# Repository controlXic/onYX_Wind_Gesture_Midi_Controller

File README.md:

# onYX

### Full Function Description:

OnYX is a highly versatile and ergonomic MIDI controller that combines the functionalities of wind controllers, pad controllers and gesture controllers.

It consists of 4 pieces:

* the mouthpiece: includes an air pressure sensor with which we control the Velocity, Breath Controller (CC2), Volume (CC7) and Expression (CC11)

* the left handpiece: includes 4 touch sensors for the thumb and 5 more for the rest of the fingers, and a gyroscope to detect the inclination of the hand in the Y and X axes.

* the right handpiece: also includes 4 touch sensors for the thumb and 5 for the rest of the fingers, and a gyroscope to detect the inclination of the hand in the Y and X axes.

* the transducer: connects to the USB port of the computer and receives and translates the information from the mouthpiece and the handpieces into MIDI.

OnYX has been designed as a complete and versatile wind controller, allowing you to control everything that other keyboard-type controllers have allowed for years by including knobs, faders, joysticks and pads.

### Device:    

### In this sense, the main functions of OnYX include:

* Playing notes as if it was a traditional wind controller, with saxophone / flute type fingerings, and with up to 6 octaves of register (4 of them using the octave buttons on the left thumb, and 2 more using very intuitive and easy-to-master alternate fingerings).

* Quickly switch MIDI channels, allowing you to switch sounds or control between different MIDI instruments seamlessly.

* Activate and deactivate effects and functions using Control Changes.

* Control continuous parameters such as pitch bend, modulation, volume, pan by tilting your hands to mimic the knobs and faders of other controllers.

* With the appropriate program, it allows us to make chords and individually control up to 5 different notes, allowing us total control of the voicings with a freedom similar to that offered by a keyboard or guitar.

* Control drums and / or samplers as if each touch sensor was a pad, facilitating that more percussive and rhythmic control.

* OnYX is a Plug & Play instrument that works with any DAW: playing notes, playing drums with pads, pitch bend, modulation... However, to get the most out of it you should make sure that your DAW allows MIDI mapping and configure all the functions to your liking within the program itself.

### Name and inspiration
OnYX is strongly inspired by the “Beat Jazz” created by Onyx Ashanti and presented in 2011. However, he is no longer working on that concept, and his instrument was evolving in a very different direction. Furthermore, the Beat Jazz was an instrument that only worked with Linux and its own program (programmed in Pure Data). 

We have retaken that concept, and we have turned it into a MIDI controller compatible with any DAW and operating system, and totally reconfigurable thanks to MIDI mapping to adapt to the needs of each one.

We chose the name OnYX with two intentions:

1) Honor to the creator of the original idea, Onyx Ashanti.
2) Point out the most characteristic element of this controller, the gyroscopes: “Turn On the Y and X axes”

### More information
If you want to know more details and follow the evolution of this project, we invite you to follow us on Instagram: @controlxic

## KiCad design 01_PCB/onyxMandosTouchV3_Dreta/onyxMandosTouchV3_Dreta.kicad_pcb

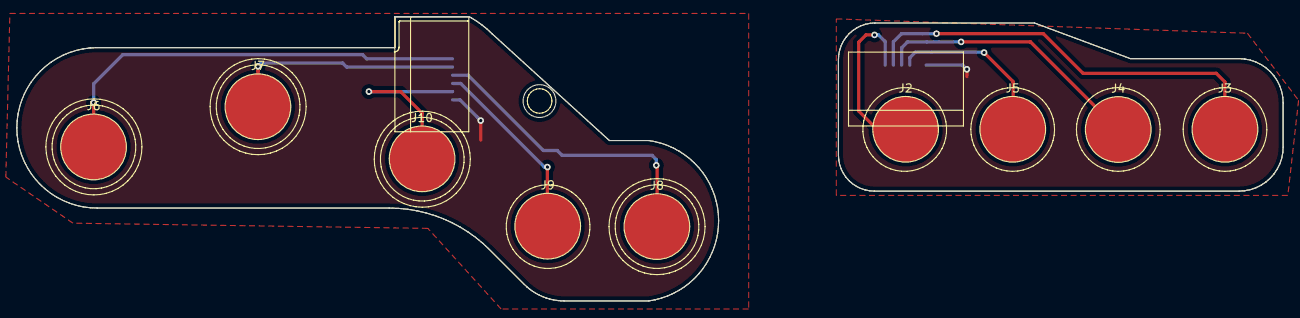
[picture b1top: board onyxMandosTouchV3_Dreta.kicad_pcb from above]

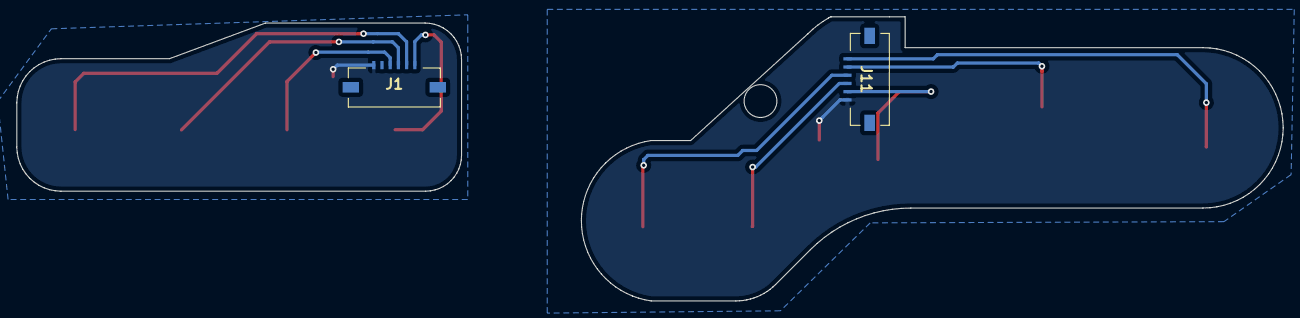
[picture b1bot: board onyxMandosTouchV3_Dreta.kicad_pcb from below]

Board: 2 copper layers, 154.3 x 34.6 mm, 11 parts (2 on the bottom side), 9 nets.

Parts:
J1, J11: 200529-0060; 2005290060
J2, J3, J4, J5, J6, J7, J8, J9, J10: Conn_01x01_Male; onYX_touch

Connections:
/K0_R: J1.6, J2.1
/K1_R: J1.5, J3.1
/K2_R: J1.4, J4.1
/K3_R: J1.3, J5.1
/K4_R: J6.1, J11.6
/K5_R: J7.1, J11.5
/K6_R: J8.1, J11.4
/K7_R: J9.1, J11.3
/K8_R: J10.1, J11.2

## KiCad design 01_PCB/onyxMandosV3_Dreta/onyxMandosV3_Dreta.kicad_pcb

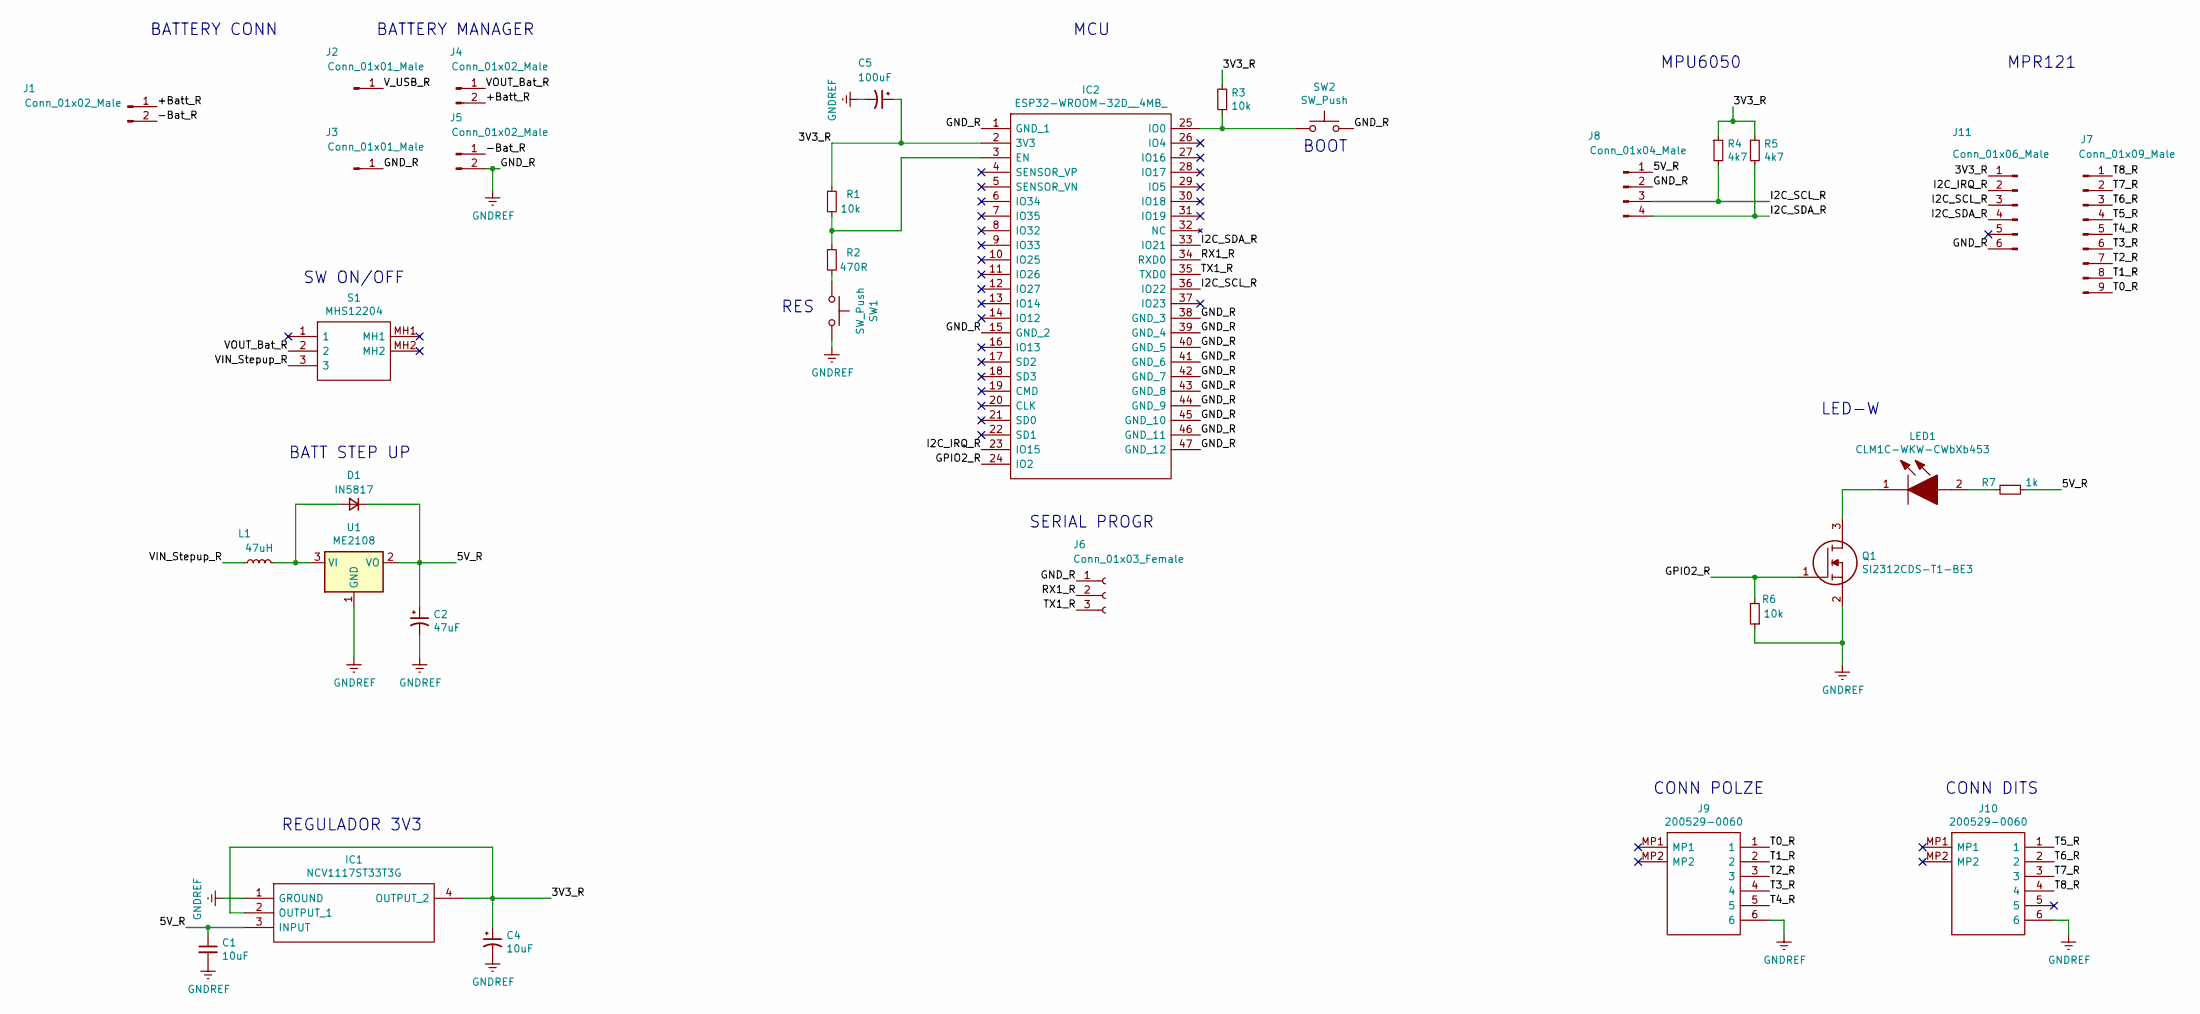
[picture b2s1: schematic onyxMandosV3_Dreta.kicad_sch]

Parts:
C1: 10uF; C_0805_2012Metric_Pad1.15x1.40mm_HandSolder
C2: 47uF; CP_EIA-3528-21_Kemet-B_Pad1.50x2.35mm_HandSolder
C4: 10uF; CP_EIA-3528-21_Kemet-B_Pad1.50x2.35mm_HandSolder
C5: 100uF; CP_EIA-3528-15_AVX-H
D1: IN5817; D_SMA
IC1: NCV1117ST33T3G; SOT230P700X180-4N; Manufacturer_Part_Number NCV1117ST33T3G; Mouser Part Number 863-NCV1117ST33T3G
IC2: ESP32-WROOM-32D__4MB_; ESP32WROOM32D4MB; Manufacturer_Part_Number ESP32-WROOM-32D (4MB); Mouser Part Number 356-ESP32WROOM-32D
J1, J4, J5: Conn_01x02_Male; PinSocket_1x02_P2.54mm_Vertical
J2, J3: Conn_01x01_Male; PinSocket_1x01_P2.54mm_Vertical
J6: Conn_01x03_Female; PinSocket_1x03_P2.54mm_Vertical
J7: Conn_01x09_Male; PinSocket_1x09_P2.54mm_Vertical
J8: Conn_01x04_Male; PinSocket_1x04_P2.54mm_Vertical
J9, J10: 200529-0060; 2005290060; Manufacturer_Part_Number 200529-0060; Mouser Part Number 538-200529-0060
J11: Conn_01x06_Male; PinHeader_1x06_P2.54mm_Vertical
L1: 47uH; L_Bourns_SRN6045TA
LED1: CLM1C-WKW-CWbXb453; LEDM3528X205N; Manufacturer_Part_Number CLM1C-WKW-CWbXb453; Mouser Part Number 941-CLM1CWKWCWBXB453
Q1: SI2312CDS-T1-BE3; SOT95P237X112-3N; Manufacturer_Part_Number SI2312CDS-T1-BE3; Mouser Part Number 78-SI2312CDS-T1-BE3
R1, R3, R6: 10k; R_0805_2012Metric_Pad1.15x1.40mm_HandSolder
R2: 470R; R_0805_2012Metric_Pad1.15x1.40mm_HandSolder
R4, R5: 4k7; R_0805_2012Metric_Pad1.15x1.40mm_HandSolder
R7: 1k; R_0805_2012Metric_Pad1.15x1.40mm_HandSolder
S1: MHS12204; Manufacturer_Part_Number MHS12204; Mouser Part Number 506-MHS12204
SW1, SW2: SW_Push; SW_SPST_CK_RS282G05A3
U1: ME2108; SOT-89-3

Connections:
/3V3_R: C4.1, C5.1, IC1.2 (OUTPUT_1), IC1.4 (OUTPUT_2), IC2.2 (3V3), J11.1, R1.1, R3.2, R4.1, R5.1
/5V_R: C1.1, C2.1, D1.1 (K), IC1.3 (INPUT), J8.1, R7.1, U1.2 (VO)
/+Batt_R: J1.1, J4.2
/-Bat_R: J1.2, J5.1
/GPIO2_R: IC2.24 (IO2), Q1.1, R6.2
/I2C_IRQ_R: IC2.23 (IO15), J11.2
/I2C_SCL_R: IC2.36 (IO22), J8.3, J11.3, R4.2
/I2C_SDA_R: IC2.33 (IO21), J8.4, J11.4, R5.2
/RX1_R: IC2.34 (RXD0), J6.2
/T0_R: J7.9, J9.1
/T1_R: J7.8, J9.2
/T2_R: J7.7, J9.3
/T3_R: J7.6, J9.4
/T4_R: J7.5, J9.5
/T5_R: J7.4, J10.1
/T6_R: J7.3, J10.2
/T7_R: J7.2, J10.3
/T8_R: J7.1, J10.4
/TX1_R: IC2.35 (TXD0), J6.3
/VIN_Stepup_R: L1.1, S1.3
/VOUT_Bat_R: J4.1, S1.2
/V_USB_R: J2.1
GNDREF: C1.2, C2.2, C4.2, C5.2, IC1.1 (GROUND), IC2.1 (GND_1), IC2.15 (GND_2), IC2.38 (GND_3), IC2.39 (GND_4), IC2.40 (GND_5), IC2.41 (GND_6), IC2.42 (GND_7), IC2.43 (GND_8), IC2.44 (GND_9), IC2.45 (GND_10), IC2.46 (GND_11), IC2.47 (GND_12), J3.1, J5.2, J6.1, J8.2, J9.6, J10.6, J11.6, Q1.2, R6.1, SW1.2, SW2.2, U1.1 (GND)
unnamed: D1.2 (A), L1.2, U1.3 (VI)
unnamed: IC2.3 (EN), R1.2, R2.1
unnamed: IC2.25 (IO0), R3.1, SW2.1
unnamed: LED1.1, Q1.3
unnamed: LED1.2, R7.2
unnamed: R2.2, SW1.1

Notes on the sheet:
MPR121
BATTERY MANAGER
MPU6050
CONN POLZE
BATT STEP UP
MCU
BOOT
LED-W
BATTERY CONN
RES
CONN DITS
SW ON/OFF
REGULADOR 3V3
SERIAL PROGR

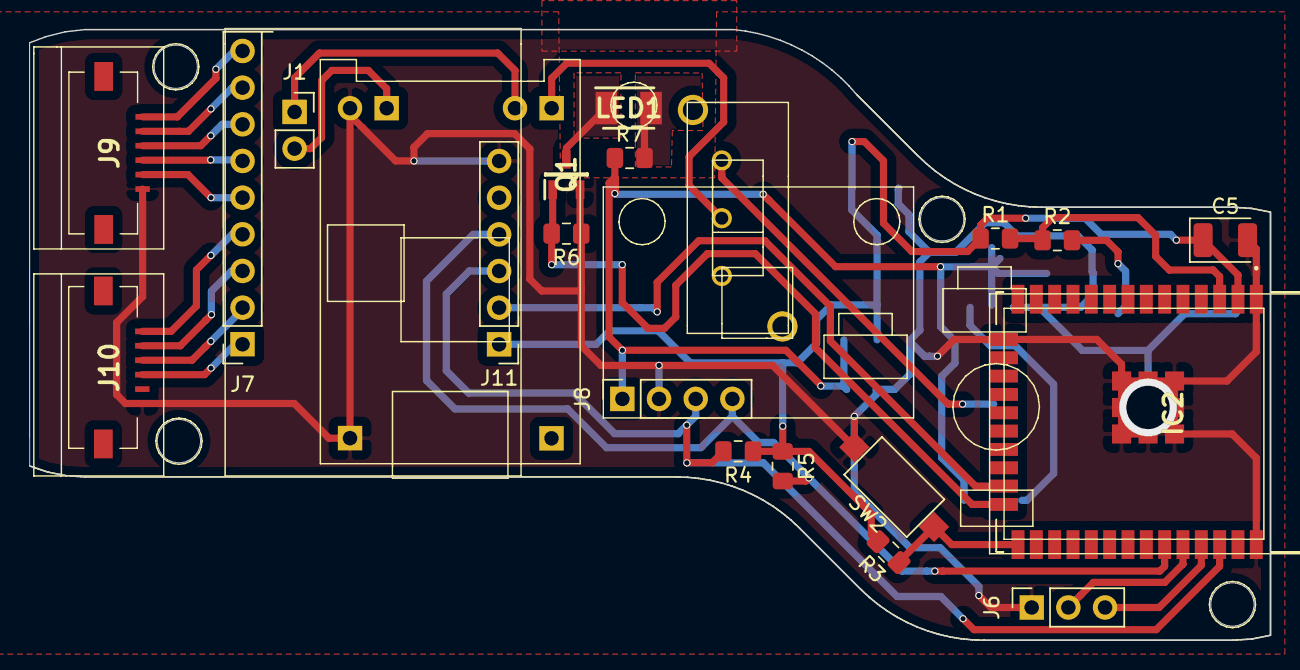
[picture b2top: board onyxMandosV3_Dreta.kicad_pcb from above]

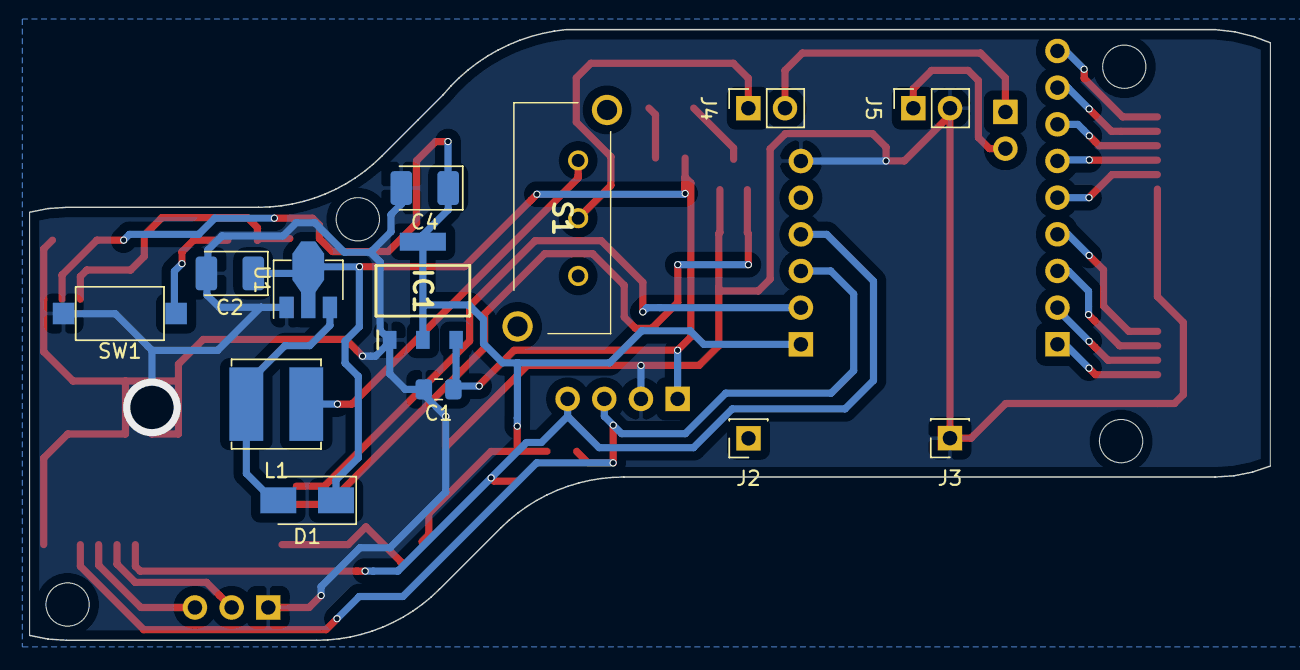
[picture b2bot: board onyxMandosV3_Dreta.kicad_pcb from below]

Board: 2 copper layers, 86.0 x 42.3 mm, 32 parts (13 on the bottom side), 28 nets.

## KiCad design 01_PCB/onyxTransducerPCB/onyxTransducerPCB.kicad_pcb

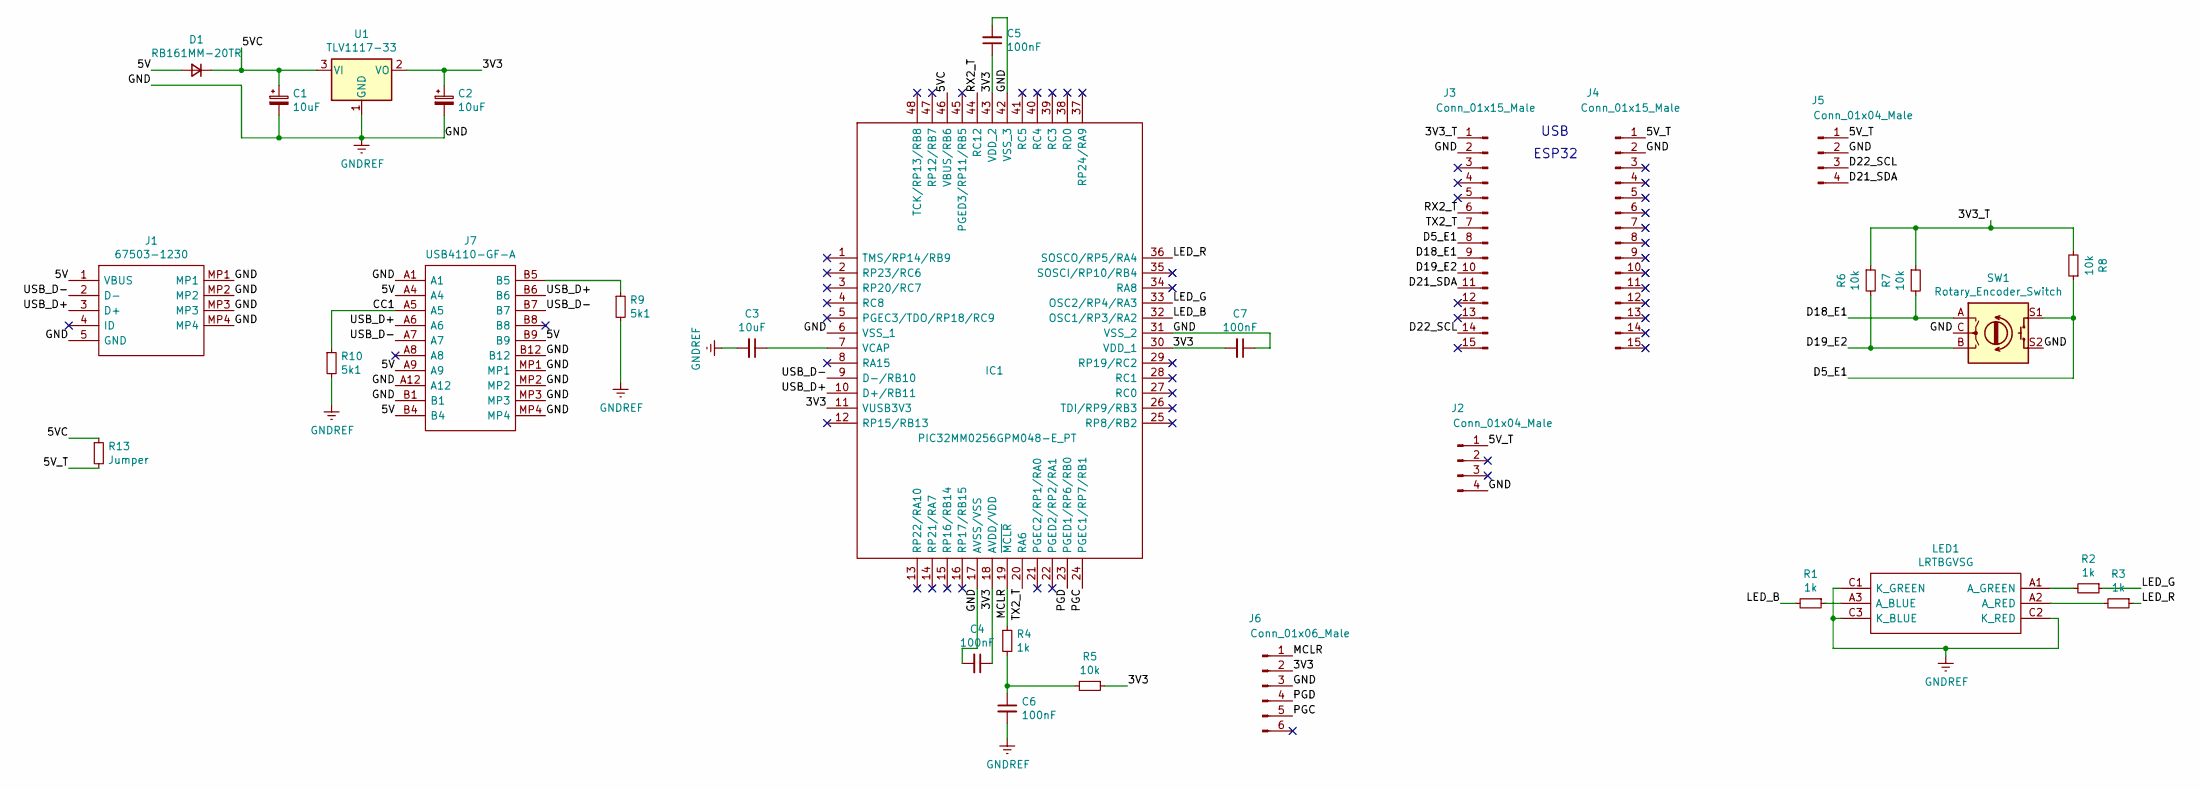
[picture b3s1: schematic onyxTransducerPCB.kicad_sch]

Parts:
C1, C2: 10uF; CP_EIA-3216-18_Kemet-A
C3: 10uF; C_0805_2012Metric_Pad1.15x1.40mm_HandSolder
C4, C5, C6, C7: 100nF; C_0805_2012Metric_Pad1.15x1.40mm_HandSolder
D1: RB161MM-20TR; D_SOD-123F
IC1: PIC32MM0256GPM048-E_PT; QFP50P900X900X120-48N; Manufacturer_Part_Number PIC32MM0256GPM048-E/PT; Mouser Part Number 579-MM0256GPM048E/PT
J1: 67503-1230; 675031230; Manufacturer_Part_Number 67503-1230; Mouser Part Number 538-67503-1230
J2, J5: Conn_01x04_Male; PinHeader_1x04_P2.54mm_Vertical
J3, J4: Conn_01x15_Male; PinHeader_1x15_P2.54mm_Vertical
J6: Conn_01x06_Male; PinSocket_1x06_P2.54mm_Vertical
J7: USB4110-GF-A; USB4110GFA; Manufacturer_Part_Number USB4110-GF-A; Mouser Part Number 640-USB4110-GF-A
LED1: LRTBGVSG; Manufacturer_Part_Number LRTBGVSG
R1, R2, R3, R4: 1k; R_0805_2012Metric_Pad1.15x1.40mm_HandSolder
R5, R6, R7, R8: 10k; R_0805_2012Metric_Pad1.15x1.40mm_HandSolder
R9, R10: 5k1; R_0805_2012Metric_Pad1.15x1.40mm_HandSolder
R13: Jumper; R_0805_2012Metric_Pad1.15x1.40mm_HandSolder
SW1: Rotary_Encoder_Switch; RotaryEncoder_Alps_EC11E-Switch_Vertical_H20mm
U1: TLV1117-33; SOT-223-3_TabPin2

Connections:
/3V3: C2.1, C4.1, C5.1, C7.2, IC1.11 (VUSB3V3), IC1.18 (AVDD/VDD), IC1.30 (VDD_1), IC1.43 (VDD_2), J6.2, R5.1, U1.2 (VO)
/3V3_T: J3.1, R6.1, R7.1, R8.2
/5V: D1.2 (A), J1.1 (VBUS), J7.A4, J7.A9, J7.B4, J7.B9; also elsewhere on the board
/5VC: C1.1, D1.1 (K), IC1.46 (VBUS/RB6), R13.1, U1.3 (VI)
/5V_T: J2.1, J4.1, J5.1, R13.2
/CC1: J7.A5, R10.1
/D5_E1: J3.8, R8.1, SW1.S1
/D18_E1: J3.9, R7.2, SW1.A
/D19_E2: J3.10, R6.2, SW1.B
/D21_SDA: J3.11, J5.4
/D22_SCL: J3.14, J5.3
/LED_B: IC1.32 (OSC1/RP3/RA2), R1.2
/LED_G: IC1.33 (OSC2/RP4/RA3), R2.1
/LED_R: IC1.36 (SOSCO/RP5/RA4), R3.1
/MCLR: IC1.19 (~MCLR), J6.1, R4.1
/PGC: IC1.24 (PGEC1/RP7/RB1), J6.5
/PGD: IC1.23 (PGED1/RP6/RB0), J6.4
/RX2_T: IC1.44 (RC12), J3.6
/TX2_T: IC1.20 (RA6), J3.7
/USB_D+: IC1.10 (D+/RB11), J1.3 (D+), J7.A6, J7.B6
/USB_D-: IC1.9 (D-/RB10), J1.2 (D-), J7.A7, J7.B7
GNDREF: C1.2, C2.2, C3.2, C4.2, C5.2, C6.2, C7.1, IC1.6 (VSS_1), IC1.17 (AVSS/VSS), IC1.31 (VSS_2), IC1.42 (VSS_3), J1.5 (GND), J1.MP1, J1.MP2, J1.MP3, J1.MP4, J2.4, J3.2, J4.2, J5.2, J6.3, J7.A1, J7.A12, J7.B1, J7.B12, J7.MP1, J7.MP2, J7.MP3, J7.MP4, LED1.C1 (K_GREEN), LED1.C2 (K_RED), LED1.C3 (K_BLUE), R9.2, R10.2, SW1.C, SW1.S2, U1.1 (GND); also elsewhere on the board
unnamed: C3.1, IC1.7 (VCAP)
unnamed: C6.1, R4.2, R5.2
unnamed: J7.B5, R9.1
unnamed: LED1.A1 (A_GREEN), R2.2
unnamed: LED1.A2 (A_RED), R3.2
unnamed: LED1.A3 (A_BLUE), R1.1

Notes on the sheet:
ESP32
USB

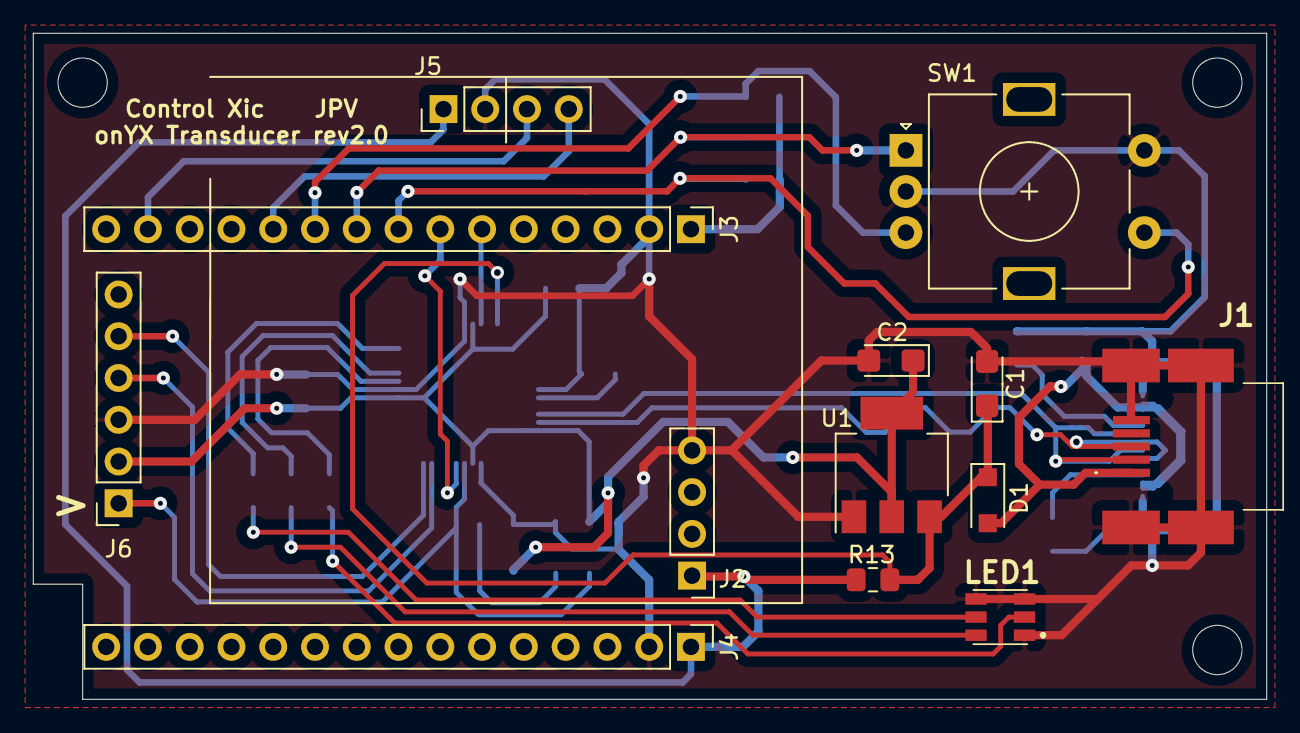
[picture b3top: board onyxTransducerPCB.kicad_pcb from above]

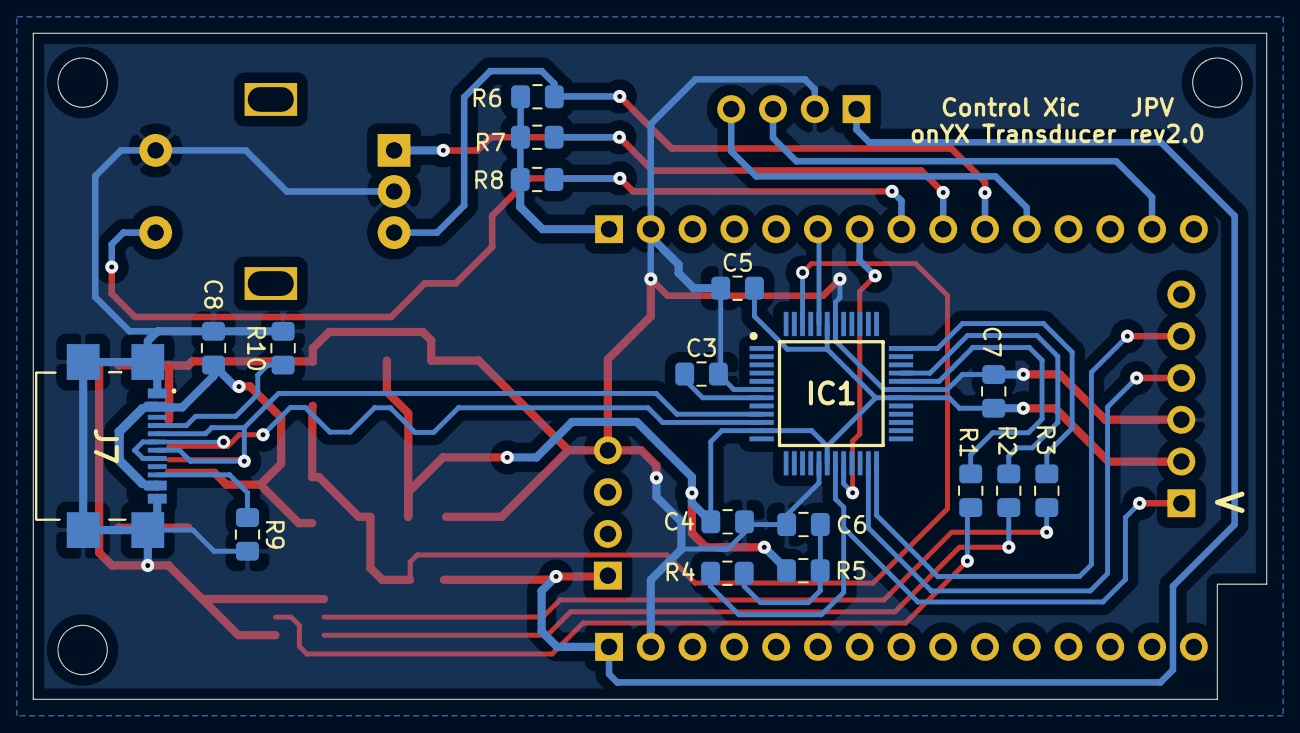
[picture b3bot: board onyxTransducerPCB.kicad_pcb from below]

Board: 2 copper layers, 75.0 x 40.5 mm, 31 parts (18 on the bottom side), 28 nets.

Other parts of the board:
C8: 100nF; C_0805_2012Metric_Pad1.15x1.40mm_HandSolder

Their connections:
/5V: C8.2; also elsewhere on the board
GNDREF: C8.1; also elsewhere on the board

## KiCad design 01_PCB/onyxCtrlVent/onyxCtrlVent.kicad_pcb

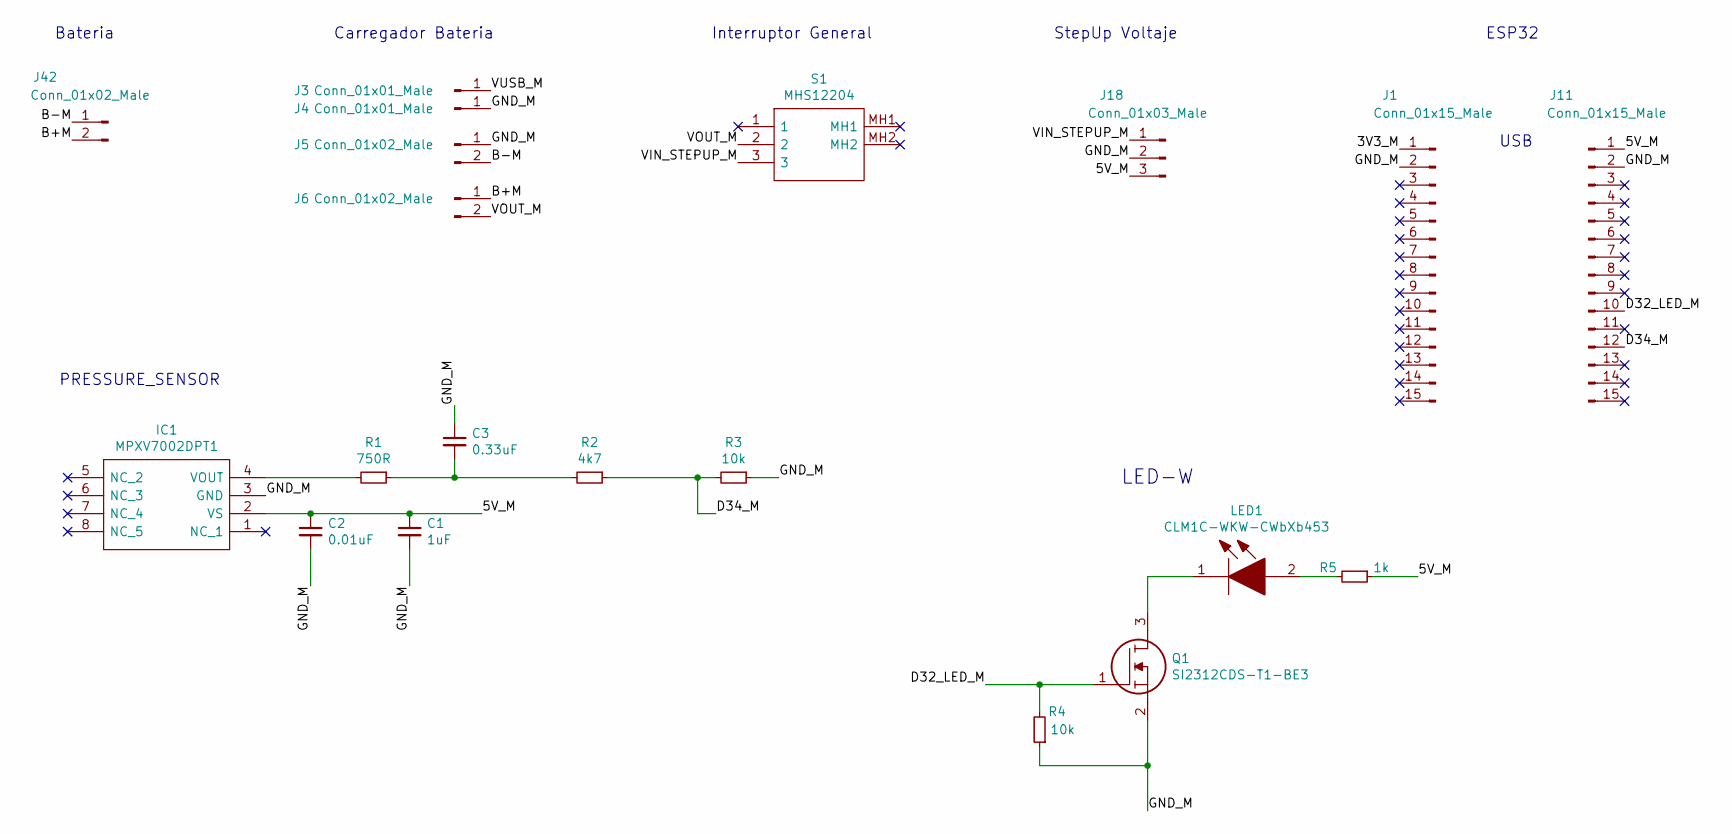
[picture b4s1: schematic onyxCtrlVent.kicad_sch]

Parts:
C1: 1uF; C_0805_2012Metric_Pad1.15x1.40mm_HandSolder
C2: 0.01uF; C_0805_2012Metric_Pad1.15x1.40mm_HandSolder
C3: 0.33uF; C_0805_2012Metric_Pad1.15x1.40mm_HandSolder
IC1: MPXV7002DPT1; Manufacturer_Part_Number MPXV7002DPT1; Mouser Part Number 841-MPXV7002DPT1
J1, J11: Conn_01x15_Male; PinHeader_1x15_P2.54mm_Vertical
J3, J4: Conn_01x01_Male; PinHeader_1x01_P2.54mm_Vertical
J5, J6, J42: Conn_01x02_Male; PinHeader_1x02_P2.54mm_Vertical
J18: Conn_01x03_Male; PinHeader_1x03_P2.54mm_Vertical
LED1: CLM1C-WKW-CWbXb453; LEDM3528X205N; Manufacturer_Part_Number CLM1C-WKW-CWbXb453; Mouser Part Number 941-CLM1CWKWCWBXB453
Q1: SI2312CDS-T1-BE3; SOT95P237X112-3N; Manufacturer_Part_Number SI2312CDS-T1-BE3; Mouser Part Number 78-SI2312CDS-T1-BE3
R1: 750R; R_0805_2012Metric_Pad1.15x1.40mm_HandSolder
R2: 4k7; R_0805_2012Metric_Pad1.15x1.40mm_HandSolder
R3, R4: 10k; R_0805_2012Metric_Pad1.15x1.40mm_HandSolder
R5: 1k; R_0805_2012Metric_Pad1.15x1.40mm_HandSolder
S1: MHS12204; Manufacturer_Part_Number MHS12204; Mouser Part Number 506-MHS12204

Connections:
/3V3_M: J1.1
/5V_M: C1.1, C2.1, IC1.2 (VS), J11.1, J18.3, R5.1
/B+M: J6.1, J42.2
/B-M: J5.2, J42.1
/D32_LED_M: J11.10, Q1.1, R4.2
/D34_M: J11.12, R2.1, R3.2
/GND_M: C1.2, C2.2, C3.1, IC1.3 (GND), J1.2, J4.1, J5.1, J11.2, J18.2, Q1.2, R3.1, R4.1
/VIN_STEPUP_M: J18.1, S1.3
/VOUT_M: J6.2, S1.2
/VUSB_M: J3.1
unnamed: C3.2, R1.1, R2.2
unnamed: IC1.4 (VOUT), R1.2
unnamed: LED1.1, Q1.3
unnamed: LED1.2, R5.2

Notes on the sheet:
ESP32
Bateria
PRESSURE_SENSOR
Interruptor General
StepUp Voltaje
LED-W
USB
Carregador Bateria

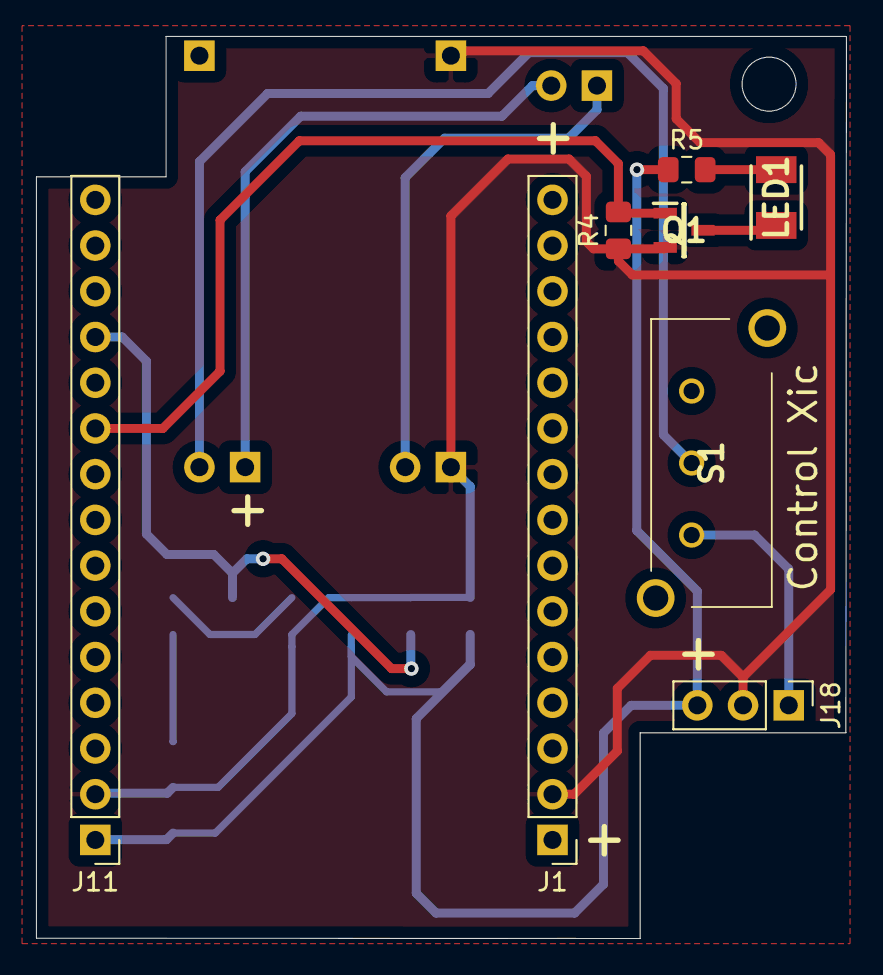
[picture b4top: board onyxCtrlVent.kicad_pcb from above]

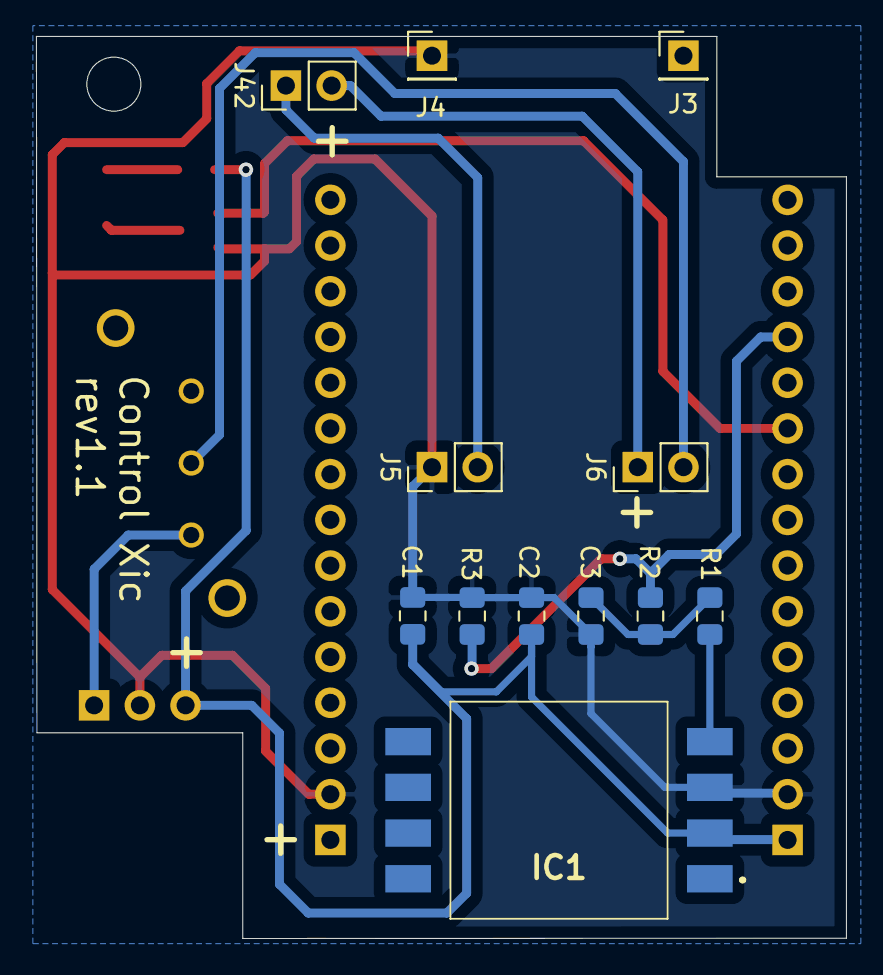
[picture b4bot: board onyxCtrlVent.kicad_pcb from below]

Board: 2 copper layers, 45.0 x 50.1 mm, 20 parts (12 on the bottom side), 12 nets.

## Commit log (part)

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2021-06-18 Images
    rev 1.0
2021-06-18 Add files via upload
    Case
    rev1.0
